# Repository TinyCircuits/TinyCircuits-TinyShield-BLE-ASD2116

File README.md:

# TinyCircuits Bluetooth Low Energy (BLE) TinyShield, ASD2116
# ASD2116 Rev2

The design files are located under design_files/ for the TinyCircuits ASD2116 Rev 2 PCB. This is a TinyShield board that has a BlueNRG-MS module, local power supply and level shifters to connect between the TinyDuino and BLE mod

Format is in Cadsoft Eagle format - Eagle version 6.3 was used for the original design.

For more information on this, check out the product page at TinyCircuits.com: https://tinycircuits.com/collections/communication/products/bluetooth-low-energy-tinyshield

# License

Design by TinyCircuits.
All design files are released under the Creative Commons Attribution Share-Alike 3.0 License, see the following link for details: http://creativecommons.org/licenses/by-sa/3.0

All text above must be included in any redistribution or derived design

This project uses designs and concepts developed as part of the Arduino project and the LilyPad project.  The TinyCircuits design files themselves (schematics, PCB and libraries) are not directly derived from these works' design files and have been created new, however the concepts and basic architecture behind the TinyDuino and TinyLily products are derived and we thank the hard work of the organizations below for their contributions to open-source hardware:
  
Original Arduino Uno Design by Team Arduino

LilyPad Arduino Design by Leah Buechley and Sparkfun Electronics

Please support the open-source hardware community

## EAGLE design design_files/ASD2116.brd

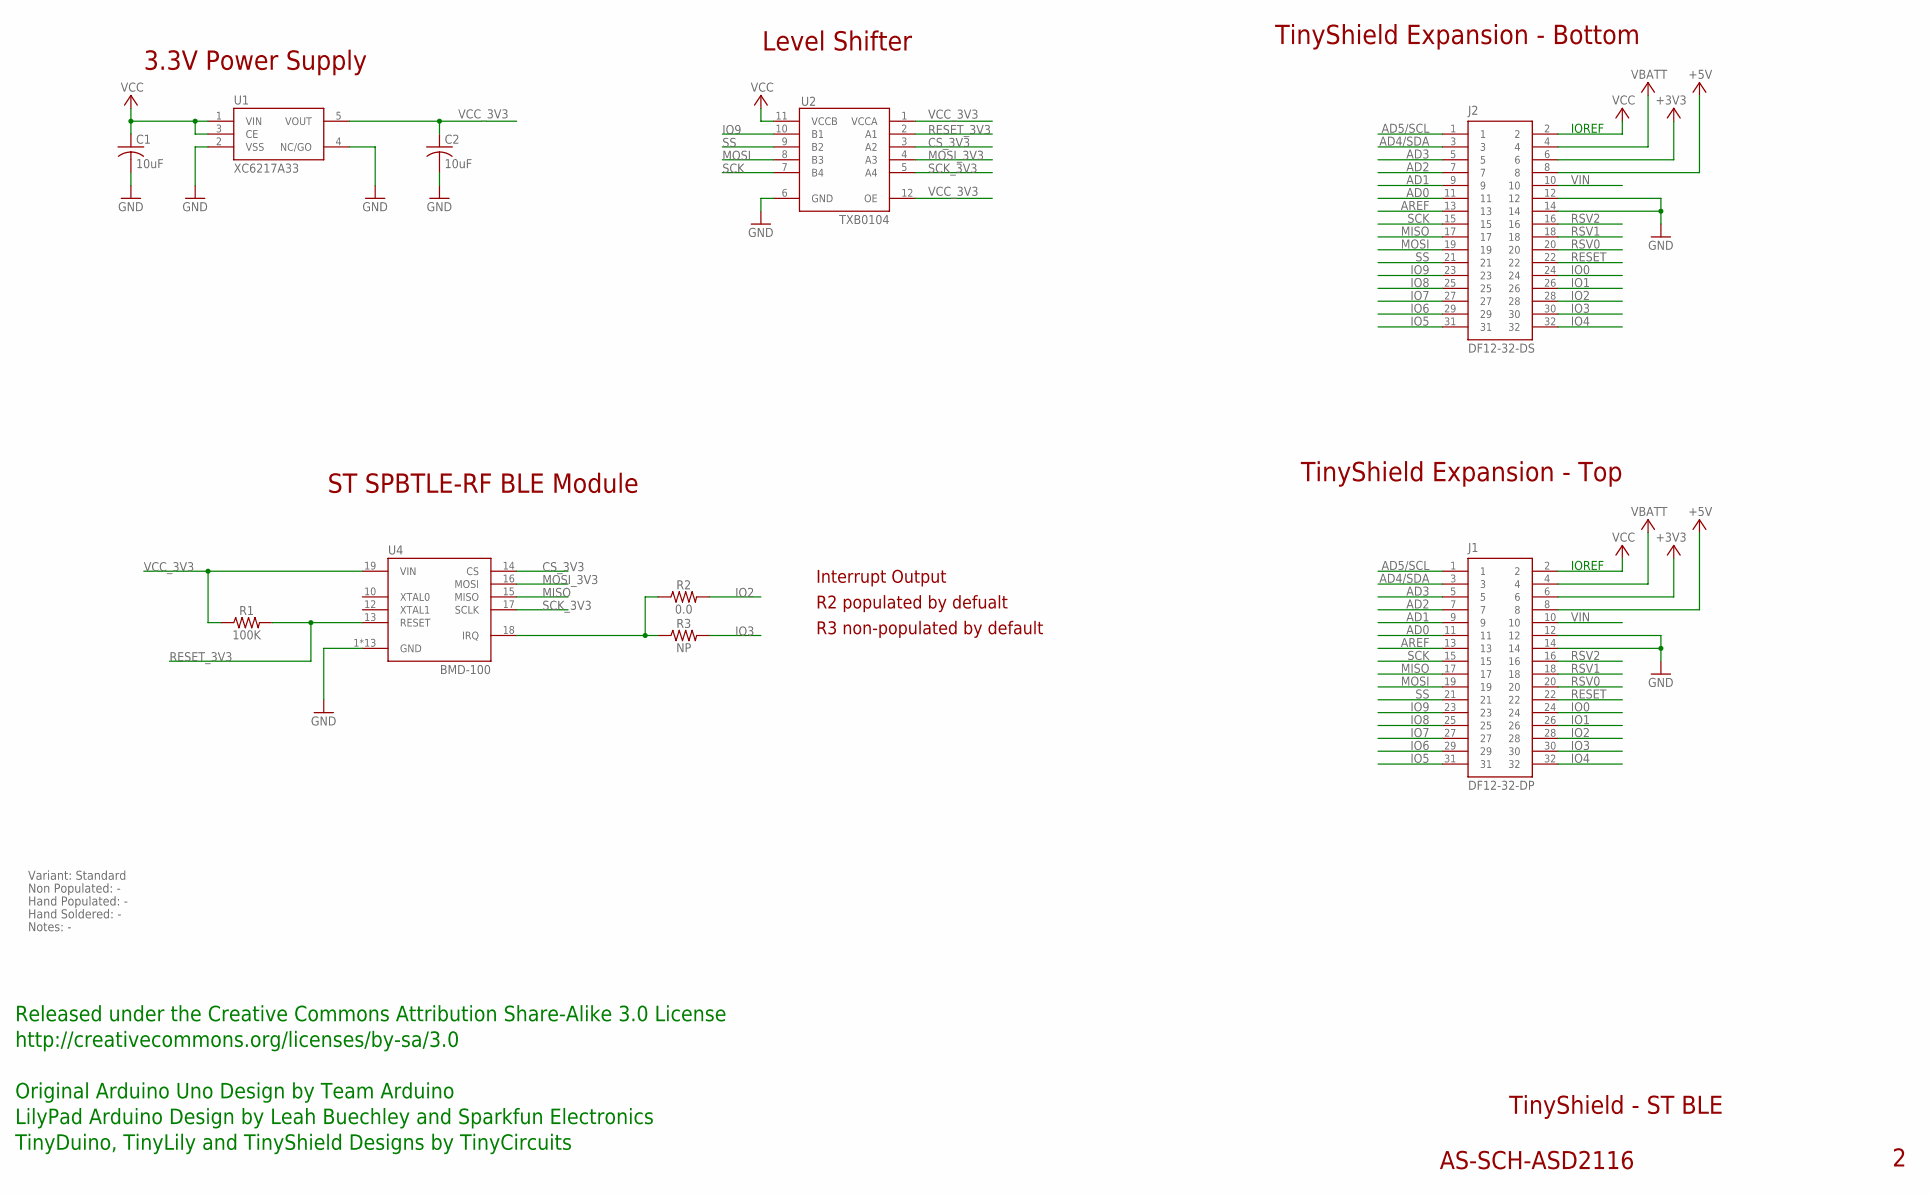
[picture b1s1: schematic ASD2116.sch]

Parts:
C1, C2: 10uF; C0603; PARTNO AS-ITM-00002
J1: DF12-32-DP; PARTNO AS-ITM-00015
J2: DF12-32-DS; PARTNO AS-ITM-00012
R1: 100K; 0402
R2: 0.0; 0402; PARTNO AS-ITM-00076
R3: NP; 0402; PARTNO AS-ITM-00076
U1: XC6217A33; SOT-25; PARTNO AS-ITM-00249
U2: TXB0104; UQFN-12
U4: BMD-100

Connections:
+3V3: J1.6, J2.6
+5V: J1.8, J2.8
AD0: J1.11, J2.11
AD1: J1.9, J2.9
AD2: J1.7, J2.7
AD3: J1.5, J2.5
AD4/SDA: J1.3, J2.3
AD5/SCL: J1.1, J2.1
AREF: J1.13, J2.13
CS_3V3: U2.3 (A2), U4.14 (CS)
GND: C1.2, C2.2, J1.12, J1.14, J2.12, J2.14, U1.2 (VSS), U1.4 (NC/GO), U2.6 (GND), U4.1 (GND), U4.2 (GND), U4.3 (GND), U4.7 (GND), U4.9 (GND), U4.11 (GND), U4.20 (GND), U4.A (GND), U4.B (GND), U4.C (GND), U4.D (GND), U4.E (GND), U4.F (GND)
IO0: J1.24, J2.24
IO1: J1.26, J2.26
IO2: J1.28, J2.28, R2.2
IO3: J1.30, J2.30, R3.2
IO4: J1.32, J2.32
IO5: J1.31, J2.31
IO6: J1.29, J2.29
IO7: J1.27, J2.27
IO8: J1.25, J2.25
IO9: J1.23, J2.23, U2.10 (B1)
IRQ: R2.1, R3.1, U4.18 (IRQ)
MISO: J1.17, J2.17, U4.15 (MISO)
MOSI: J1.19, J2.19, U2.8 (B3)
MOSI_3V3: U2.4 (A3), U4.16 (MOSI)
RESET: J1.22, J2.22
RESET_3V3: R1.2, U2.2 (A1), U4.13 (RESET)
RSV0: J1.20, J2.20
RSV1: J1.18, J2.18
RSV2: J1.16, J2.16
SCK: J1.15, J2.15, U2.7 (B4)
SCK_3V3: U2.5 (A4), U4.17 (SCLK)
SS: J1.21, J2.21, U2.9 (B2)
VBATT: J1.4, J2.4
VCC: C1.1, J1.2, J2.2, U1.1 (VIN), U1.3 (CE), U2.11 (VCCB)
VCC_3V3: C2.1, R1.1, U1.5 (VOUT), U2.1 (VCCA), U2.12 (OE), U4.19 (VIN)
VIN: J1.10, J2.10

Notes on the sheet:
TinyShield Expansion - Bottom
TinyShield - ST BLE
AS-SCH-ASD2116
TinyShield Expansion - Top
IOREF
Released under the Creative Commons Attribution Share-Alike 3.0 License
http://creativecommons.org/licenses/by-sa/3.0
LilyPad Arduino Design by Leah Buechley and Sparkfun Electronics
TinyDuino, TinyLily and TinyShield Designs by TinyCircuits
Original Arduino Uno Design by Team Arduino
3.3V Power Supply
ST SPBTLE-RF BLE Module
Level Shifter
Interrupt Output
R2 populated by defualt
R3 non-populated by default
Variant: Standard
Non Populated: -
Hand Populated: -
Hand Soldered: -
Notes: -

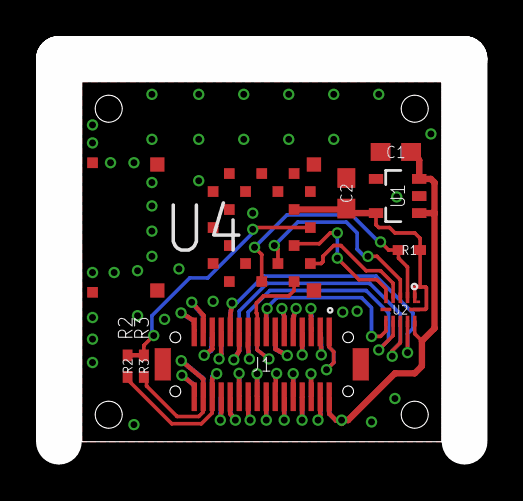
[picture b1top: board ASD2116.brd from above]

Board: 2 copper layers, 20.0 x 20.0 mm, 11 parts (1 on the bottom side), 37 nets.

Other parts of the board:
U$1: DOCFIELD-TINYCIRCUITS-PCB

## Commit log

2017-02-21 :confetti_ball: Added .gitattributes & .gitignore files
2017-02-21 Rev 1
    Initial commit for the schematics.
2017-02-21 Obsolete
2019-01-02 update format
2019-01-07 updated comments
2019-01-10 add zip file
2019-01-10 add tutorial images
2019-01-10 add pictures
2019-04-19 better pic
2019-05-22 added images
2019-05-23 updated images
2020-02-11 image update
2020-07-28 Add CAD data
2020-08-14 Update CAD drawing
2022-01-19 update datasheet
